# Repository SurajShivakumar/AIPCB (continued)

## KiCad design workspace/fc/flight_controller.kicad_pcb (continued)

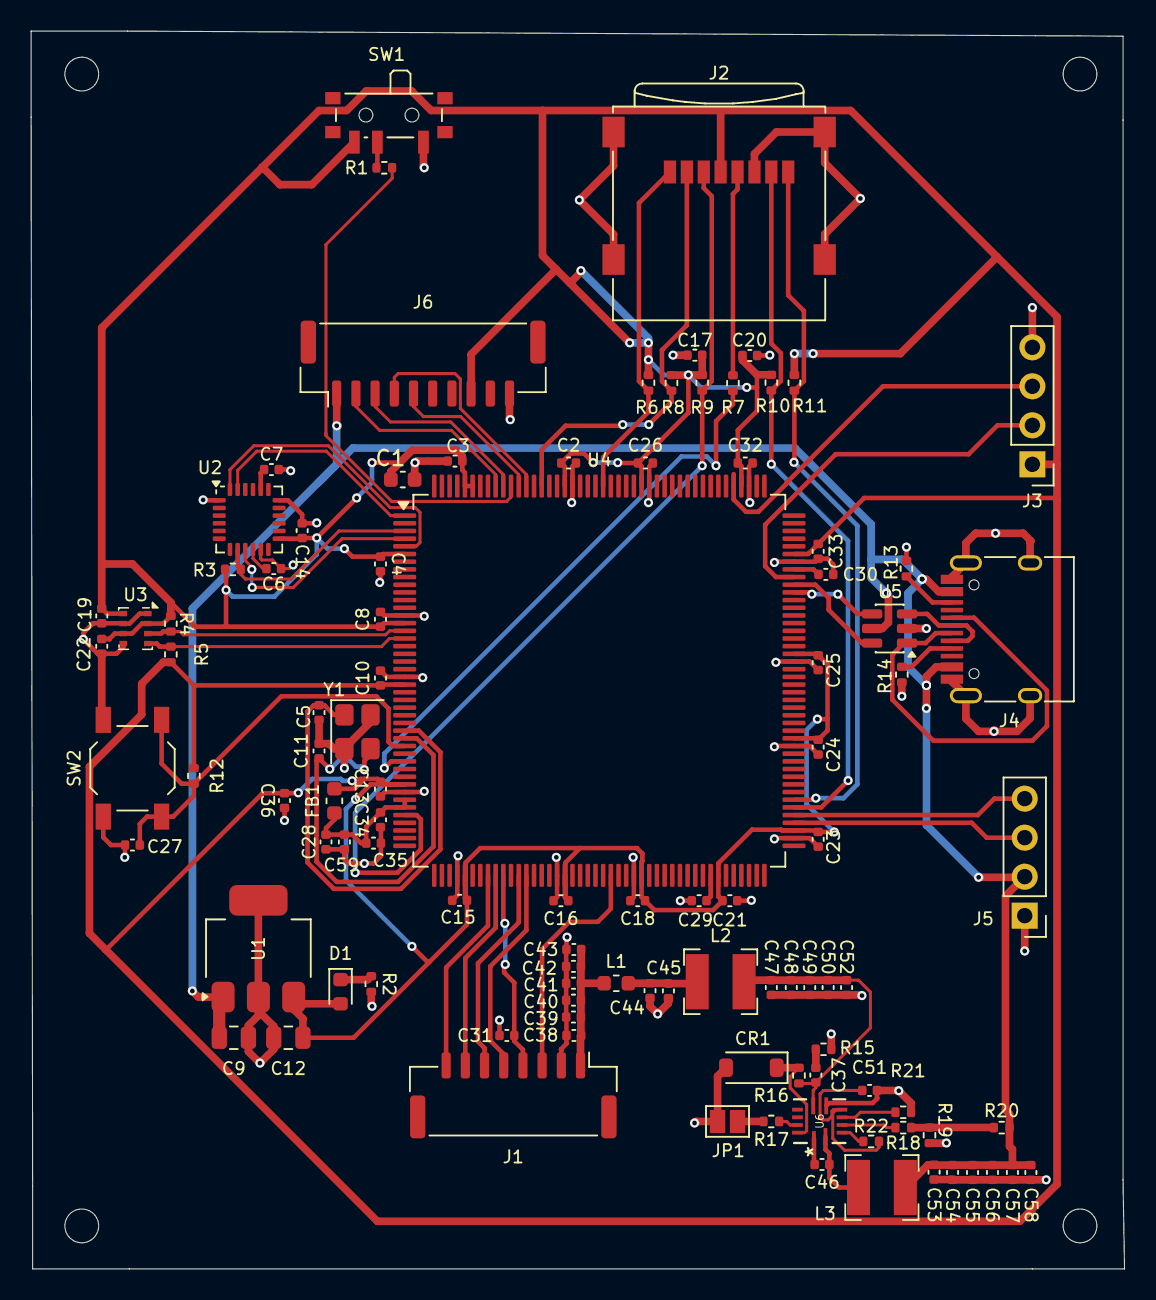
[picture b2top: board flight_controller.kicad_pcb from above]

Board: 4 copper layers, 71.2 x 80.6 mm, 107 parts (0 on the bottom side), 61 nets.

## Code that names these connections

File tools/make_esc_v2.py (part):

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# gates + phase sense (up to the power stage), then the six PWM lines to the MCU (they untangle as two
# planar groups, INH on one layer and INL on the other), then the charge pump and status pins, which can detour
# nets that cross the whole logic area: routed before the gate driver's bundles split the board in two
LONG_NETS = ["/SIG_IN", "BEMF_C", "BEMF_B", "BEMF_A", "+5V", "Net-(J1-Pin_2)", "Net-(J1-Pin_3)", "/ISENSE"]
U5_ORDER = ",".join(["Net-(U5-GHA)", "/Phase_A", "Net-(U5-GLA)", "GLB", "/Phase_B", "GHB", "GHC", "/Phase_C", "GLC",
                     "INHC", "INHB", "INHA", "INLC", "INLB", "INLA",
                     "Net-(U5-VCP)", "Net-(U5-CPH)", "Net-(U5-CPL)", "Net-(U5-DVDD)", "/VDS_LVL", "nFAULT", "ENABLE"])
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
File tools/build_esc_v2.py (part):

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# ESC is arbitrary: swapping two motor wires, or the firmware's direction setting, gives the same motor.)
CX = {"A": 11.0, "B": 24.0, "C": 37.0}
# Which side of each column the high-side FET sits on (+1 = left, -1 = right). Column B is mirrored so its gate /
# phase-sense pins on the DRV8320's top edge (GLB, SHB, GHB left to right) face LS, phase, HS in the same order:
# all three half-bridges then route to the driver without a single crossing.
SIDE = {"A": 1, "B": -1, "C": 1}

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    # charge pump right at its pins: C14 (VCP-VM) beside VCP, C16 (flying cap) at the CPH/CPL corner
    # charge pump at the lower-left corner of U5, below its phase-A pins (GHA/SHA/GLA must escape left freely)
    ("C14", 18.9, 37.6, 270, "B"), ("C13", 16.8, 36.8, 90, "B"), ("C16", 21.6, 39.5, 0, "B"),
    # R30 (VDS level) and R11 (nFAULT pull-up) sit right of U5 by the pins they serve, keeping the strip
    # between U5 and the MCU free for the six PWM lines
    ("C18", 29.0, 38.0, 90, "B"), ("R30", 30.8, 34.8, 90, "B"), ("R11", 30.8, 31.4, 90, "B"),
    # MCU + decoupling
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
